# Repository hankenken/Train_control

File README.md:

# Train_control

まずは **PC＋USBカメラ1台で車両認識と画面上の模擬制御**を確認します。
[PCでの試験手順](camera_control/PC_CAMERA_TEST_JA.md)・[検証用ZIP](camera_control/dist/Train_camera_PC_test.zip)。
画面を4回クリックして検出範囲・A/Bを登録できます。制御出力は模擬ポイントとLEDで表示し、実機へは出力しません。

現在の開発は **LattePanda 3 Delta 864・Windows 10・USBカメラ2台による検証ソフト**です。
[Windows用の導入・操作手順](camera_control/README_LATTEPANDA.md)を参照してください。撮影・画像処理・画面表示・進路選択を本体上で行う試作で、実機出力はありません。

[周辺機器の低予算案](camera_control/docs/lattepanda-budget.md)と、[通信内蔵DRV8235によるポイント制御案](camera_control/output_bridge/README.md)を追加しています。
駆動回路の設計作業は保留し、先に実カメラでの認識・模擬制御を検証します。
旧Pi版・ToF・基板設計と下記の旧シミュレーターは保留・保存しています。

---

旧シミュレーターの説明：

Nゲージ路面電車向けの進路選択シミュレーター。実機・GPIO出力はありません。

## 起動

### Windowsで開く

1. Python 3を https://www.python.org/downloads/windows/ からインストールします（Python Launcherもインストール）。
2. GitHubの「Code」→「Download ZIP」でダウンロードし、ZIPを右クリックして「すべて展開」します。
3. 展開先の `start-windows.bat` をダブルクリックします。
4. 黒い画面を開いたまま、EdgeやChromeで `http://localhost:8000` を開きます。
5. 終了するときは黒い画面で Ctrl+C を押します。

`index.html` のダブルクリックではJavaScriptのモジュールが読み込まれないため、必ずサーバー経由で開いてください。

### 開発環境

Python 3とNode.js（テスト用）を使用します。外部パッケージの導入は不要です。

```sh
cd /workspace/Train_control
npm test
npm start
```

ブラウザでサーバーの8000番ポートにアクセスします。クラウド環境では公開方法が別途必要です。

## 操作

- 上側1の外側・内側：時間差方式。A→Bが設定境界未満なら直進、以上なら分岐。
- 下側2の外側・内側：LED方式。A検知から直・曲を交互表示し、B検知時の表示で決定。
- 各組の「センサA 通過」「センサB 通過」を順に押します。
- 決定後はポイントを模擬的に切り替え、進路をロックします。「通過完了」で待機へ戻します。
- 両方式とも、A検知やLEDの交互表示ではポイントを操作しません。Bで進路を確定した時点だけ位置を更新します。通過完了後も前回位置を保持します。起動直後の位置は「未確認」です。
- 設定変更は4組とも待機中の場合のみ可能です。再読み込みで状態と設定を初期化します。

図のセンサ・ポイント位置は仮配置です。交差部での線路接続はありません。
列車の速度・停止・発車は運転者が操作します。信号は進路決定の模擬表示のみで、在線・競合進路の連動は未実装です。

## 実機化の前に

ポイント駆動と車両非加工の光センサについて、[実機回路の設計案](hardware/README.md)を参照してください。未確認の電気仕様があり、まだ通電用の確定回路ではありません。

Raspberry Pi 4 Model B、KATO 40-231を基準に設計しています。
[センサとPiの配線・取付設計](hardware/sensor-design.md)、[機種・8入力の設定例](config/pi4.example.json)を追加しました。
センサの検知フィルタは単体テスト済みですが、SPI読み取り・校正画面・既存操作盤への接続はまだありません。
センサ型番と実測による校正、ポイント駆動条件、信号の仕様は今後確定します。
ポイント切替完了の確認、列車通過・在線検知、競合進路の排他、入力のチャタリング対策を追加してから実機出力を実装します。
GPIOにポイントの駆動負荷を直接接続しないでください。

ポイントの12V試作回路と部品表・試験手順は[駆動回路設計](hardware/turnout-driver.md)を参照してください。設定例の出力は無効のままで、実機GPIO制御は未実装です。

JLCPCB向けの[試作基板データ・実装依頼準備](hardware/pcb/README.md)を追加しました。
100×100mm・2層の3.3V制御基板で、8センサ入力と4系統のパルス制御を搭載します。
DRV8871と12V負荷回路は別置きです。信号灯の駆動回路は今回の基板に含みません。
DRC/ERCと回路図・基板の接続一致を確認済みですが、実機動作は未検証です。

最新のRev Cでは、4系統それぞれにパルス幅調整用の多回転トリマVRを追加しました。
目安は約50〜80msで、100ms以下になることを実機接続前に測定する必要があります。発注ZIP・PDFは`TC_IO_REVC`版を使用してください。

部品実装込みへ方針を変更しています。[PCBA用BOM/CPL草案と未確定事項](hardware/pcb/pcba/README.md)を確認してください。
現行はVRを含め表面実装50点の候補回路です。コネクタ部品を使わず、電線直結用の穴を残します。JLCPCBでの実装対応・部品番号・在庫・CPLの位置と回転が未確認のため、実装注文に使える確定セットではありません。

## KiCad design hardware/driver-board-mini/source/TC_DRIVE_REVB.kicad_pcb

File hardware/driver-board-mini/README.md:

# ポイント駆動基板 TC DRIVE Rev B 小型配置案

**60×45mm（暫定）・未配線・製造不可。100×100mmのRev Aと既存制御基板を変更せず、別リビジョンとして作成。**

基板面積は10,000→2,700mm²（73%減）。12V、DRV8871×4、表面実装35点、コネクタなし、制御3線×4組とポイント2線×4組、電源2線の9直付け位置を維持しています。
電気的なネット・部品値はRev Aと同一であることを検査しました。4回路入りの集約基板として詰めた配置案であり、実装・配線・熱設計後も維持できる最小寸法を保証するものではありません。

## 小型化の内容

- 4つのDRV8871を2×2配置。各チャンネルの入力・電流制限・デカップリング・100µFを近接配置。
- 大容量470µFと電源保護候補は上側へ集約。電解コンデンサを削除して面積だけ小さくする変更はしていません。
- 直付け穴は電源／コイル用が直径1.3mm・ランド3mm、制御用が直径1.0mm・ランド2mm。電線に引張り止めを設ける前提。
- 取付穴は**4個のM2用2.2mm穴**へ変更。外形から各3mm、中心間54×39mm。Rev AのM3とは互換ではありません。
- 三つの1mmフィデューシャルを追加。大半の部品記号をF.Fabへ移し、上面シルクはICと接続位置を優先。
- DDAのメーカー推奨ランド／マスク形状を維持し、プロジェクト専用フットプリントの熱逃がし穴を0.3mm、銅ランド0.6mmへ変更。各IC8穴でGNDに接続。

## 回路条件

53.6kΩ±1%による公称電流制限は約1.194A。メーカーVILIM範囲と抵抗誤差の計算では約1.090〜1.300A。
制御入力はGND/IN1/IN2、ポイントはOUT1=青／OUT2=白。青白は極性反転するため常設＋／−ではありません。
パルス幅とVR、B検知後だけの転換許可はTC IO側が担当。この基板だけで連続通電を防ぐ設計ではありません。
外部ヒューズ・保持型停止スイッチを通した12Vだけを使用し、1系統ずつ駆動します。
SS34、SMBJ18A、470µF/35V、100µF/35V等はまだメーカー型番・調達未確定の候補。保護協調、回生エネルギー、温度特性は未検証です。

## 検査結果

- ERC：0件。
- 回路図と基板：120端子割当が一致。
- 部品値・ネット・実装対象：Rev Aから変更なし。
- 配置段階のDRC：**0件**。銅箔間隔規則0.20mm。
- 異なるネットのパッド外接矩形による距離の最小値：0.20mm（保守的な下限計算）。配線幅や許容電流の評価ではありません。
- **未接続89件、配線0本。** 熱・電流・回生・ノイズを評価する銅配線とGND面は未実装です。

0.2mm間隔のDDA信号端子付近と、電源・負荷の太い配線、裏面GND面、熱逃がしを両立させることが次工程です。
小型化したことで放熱余裕が減る可能性があるため、配線時に面積や寸法の再調整が必要になる場合があります。
必要な露出パッドのはんだ付け、熱逃がし穴のマスク／ペースト／ビア充填の実装条件もJLCPCBと照合します。

## 資料

- `source/TC_DRIVE_REVB.kicad_sch` / `.kicad_pcb`：回路図と未配線の基板。
- `source/BOM_DRAFT.csv` / `connections.csv`：部品表・接続表。
- `review/TC_DRIVE_REVB_design_DRAFT.pdf`：概要・部品表・回路図・配置図。
- `reports/draft-checks.json`：寸法、部品数、検査範囲、ソースハッシュ。
- `build_design.py`→`verify_draft.py`→`export_documents.py`の順で再生成。

発注用ガーバー・最終BOM/CPLは出力していません。現在JLCPCBで確認中の100mm角制御基板の配置補正には影響しません。

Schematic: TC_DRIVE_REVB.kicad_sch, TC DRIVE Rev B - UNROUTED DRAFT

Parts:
C1: 470uF_35V_SMD_CANDIDATE; CP_Elec_10x10.5
C2, C4, C6, C8: 100nF_50V_X7R; C_0805_2012Metric
C3, C5, C7, C9: 100uF_35V_SMD_CANDIDATE; CP_Elec_6.3x7.7
D1: SS34_CANDIDATE; D_SMA
D2: SMBJ18A_CANDIDATE; D_SMB
J1: 12V_IN_AFTER_EXTERNAL_FUSE_AND_STOP; Power2; not fitted
J2: CONTROL_UP_OUT; Control3; not fitted
J3: CONTROL_UP_IN; Control3; not fitted
J4: CONTROL_LOW_OUT; Control3; not fitted
J5: CONTROL_LOW_IN; Control3; not fitted
J6: TURNOUT_UP_OUT; Power2; not fitted
J7: TURNOUT_UP_IN; Power2; not fitted
J8: TURNOUT_LOW_OUT; Power2; not fitted
J9: TURNOUT_LOW_IN; Power2; not fitted
R1, R2, R3, R4: 53.6k_1%; R_0805_2012Metric
R5, R7, R9, R11, R13, R15, R17, R19: 100R_1%; R_0805_2012Metric
R6, R8, R10, R12, R14, R16, R18, R20: 10k_1%; R_0805_2012Metric
U1, U2, U3, U4: DRV8871DDAR; DRV8871_DDA_ThermalVias_0p3

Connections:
GND: C1.2 (MINUS), C2.2, C3.2 (MINUS), C4.2, C5.2 (MINUS), C6.2, C7.2 (MINUS), C8.2, C9.2 (MINUS), D2.2 (A), J1.2, J2.1, J3.1, J4.1, J5.1, R1.2, R2.2, R3.2, R4.2, R6.2, R8.2, R10.2, R12.2, R14.2, R16.2, R18.2, R20.2, U1.1 (GND), U1.7 (PGND), U1.9 (EP_GND), U2.1 (GND), U2.7 (PGND), U2.9 (EP_GND), U3.1 (GND), U3.7 (PGND), U3.9 (EP_GND), U4.1 (GND), U4.7 (PGND), U4.9 (EP_GND)
LOW_IN_A: R17.2, R18.1, U4.3 (IN1)
LOW_IN_B: R19.2, R20.1, U4.2 (IN2)
LOW_IN_BLUE: J9.1, U4.6 (OUT1)
LOW_IN_ILIM: R4.1, U4.4 (ILIM)
LOW_IN_IN1: J5.2, R17.1
LOW_IN_IN2: J5.3, R19.1
LOW_IN_WHITE: J9.2, U4.8 (OUT2)
LOW_OUT_A: R13.2, R14.1, U3.3 (IN1)
LOW_OUT_B: R15.2, R16.1, U3.2 (IN2)
LOW_OUT_BLUE: J8.1, U3.6 (OUT1)
LOW_OUT_ILIM: R3.1, U3.4 (ILIM)
LOW_OUT_IN1: J4.2, R13.1
LOW_OUT_IN2: J4.3, R15.1
LOW_OUT_WHITE: J8.2, U3.8 (OUT2)
UP_IN_A: R9.2, R10.1, U2.3 (IN1)
UP_IN_B: R11.2, R12.1, U2.2 (IN2)
UP_IN_BLUE: J7.1, U2.6 (OUT1)
UP_IN_ILIM: R2.1, U2.4 (ILIM)
UP_IN_IN1: J3.2, R9.1
UP_IN_IN2: J3.3, R11.1
UP_IN_WHITE: J7.2, U2.8 (OUT2)
UP_OUT_A: R5.2, R6.1, U1.3 (IN1)
UP_OUT_B: R7.2, R8.1, U1.2 (IN2)
UP_OUT_BLUE: J6.1, U1.6 (OUT1)
UP_OUT_ILIM: R1.1, U1.4 (ILIM)
UP_OUT_IN1: J2.2, R5.1
UP_OUT_IN2: J2.3, R7.1
UP_OUT_WHITE: J6.2, U1.8 (OUT2)
VIN_12V: D1.2 (A), J1.1
VM: C1.1 (PLUS), C2.1, C3.1 (PLUS), C4.1, C5.1 (PLUS), C6.1, C7.1 (PLUS), C8.1, C9.1 (PLUS), D1.1 (K), D2.1 (K), U1.5 (VM), U2.5 (VM), U3.5 (VM), U4.5 (VM)

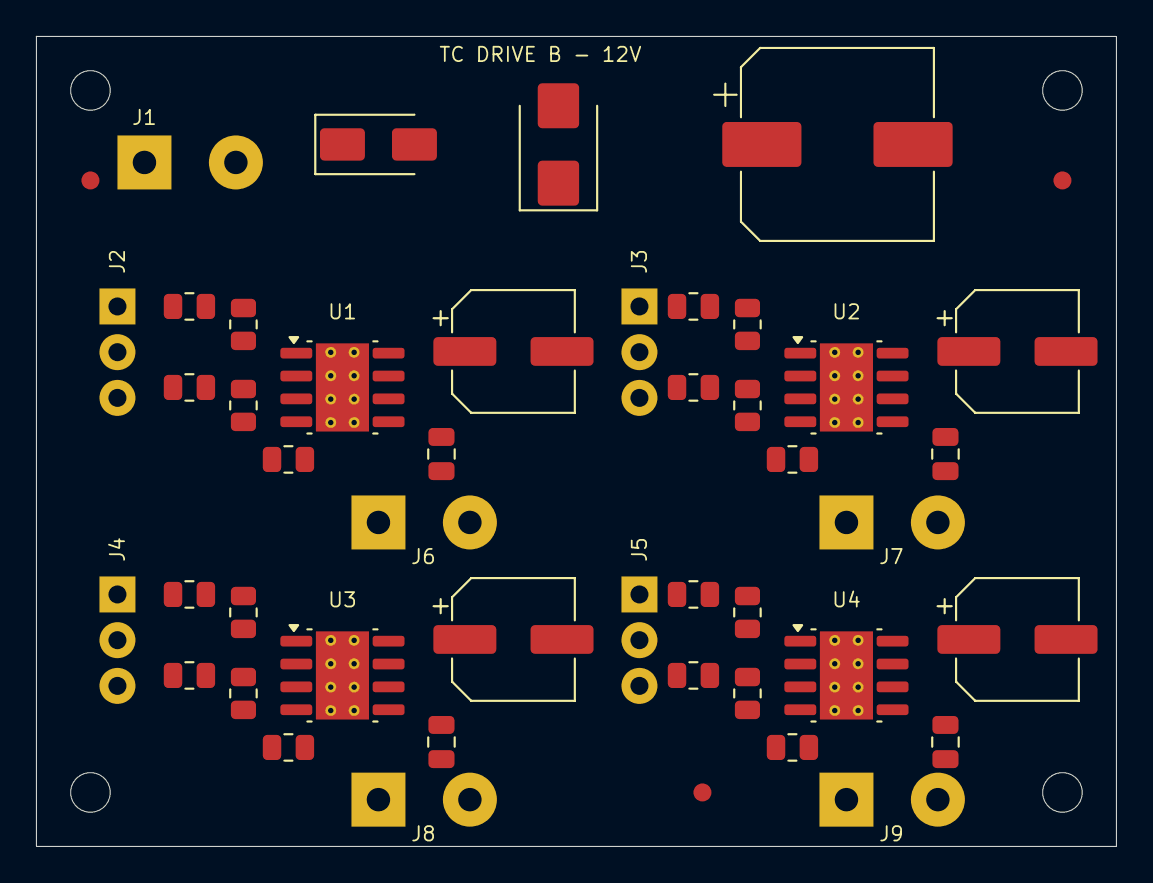
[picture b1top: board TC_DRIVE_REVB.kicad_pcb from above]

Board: 2 copper layers, 60.0 x 45.0 mm, 51 parts (0 on the bottom side), 31 nets, no tracks yet.

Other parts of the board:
FM1, FM2, FM3: Fiducial_1mm_Mask2mm
H1, H2, H3, H4: MountingHole_2.2mm_M2

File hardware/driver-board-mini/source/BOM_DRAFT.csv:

Reference,MPN_or_value,Footprint,Populate,Notes
J1,12V_IN_AFTER_EXTERNAL_FUSE_AND_STOP,TC_Wire:Power2,False,
D1,SS34_CANDIDATE,Diode_SMD:D_SMA,True,Series reverse polarity diode. Verify selected manufacturer forward loss and pulse current.
D2,SMBJ18A_CANDIDATE,Diode_SMD:D_SMB,True,Local rail clamp; pulse energy and fuse coordination not validated
C1,470uF_35V_SMD_CANDIDATE,Capacitor_SMD:CP_Elec_10x10.5,True,Bulk after polarity diode; ESR/ripple/energy verification pending
U1,DRV8871DDAR,TC_Wire:DRV8871_DDA_ThermalVias_0p3,True,TI SLVSCY9B pinout. DDA exposed pad MUST be soldered and heat-spread. Layout unrouted.
R1,53.6k_1%,Resistor_SMD:R_0805_2012Metric,True,Itrip nominal 64/53.6=1.194A; 59..69kV plus resistor 1% gives 1.090..1.300A
C2,100nF_50V_X7R,Capacitor_SMD:C_0805_2012Metric,True,Place directly at VM/PGND during final layout
C3,100uF_35V_SMD_CANDIDATE,Capacitor_SMD:CP_Elec_6.3x7.7,True,"Local bulk; candidate footprint, specific supplier part not fixed"
J2,CONTROL_UP_OUT,TC_Wire:Control3,False,Matches TC IO J10-J13 GND/IN1/IN2
J6,TURNOUT_UP_OUT,TC_Wire:Power2,False,Two-wire turnout only. Blue/white polarity not yet mapped to route.
R5,100R_1%,Resistor_SMD:R_0805_2012Metric,True,
R6,10k_1%,Resistor_SMD:R_0805_2012Metric,True,Input pulldown; driver also has internal pulldown
R7,100R_1%,Resistor_SMD:R_0805_2012Metric,True,
R8,10k_1%,Resistor_SMD:R_0805_2012Metric,True,Input pulldown; driver also has internal pulldown
U2,DRV8871DDAR,TC_Wire:DRV8871_DDA_ThermalVias_0p3,True,TI SLVSCY9B pinout. DDA exposed pad MUST be soldered and heat-spread. Layout unrouted.
R2,53.6k_1%,Resistor_SMD:R_0805_2012Metric,True,Itrip nominal 64/53.6=1.194A; 59..69kV plus resistor 1% gives 1.090..1.300A
C4,100nF_50V_X7R,Capacitor_SMD:C_0805_2012Metric,True,Place directly at VM/PGND during final layout
C5,100uF_35V_SMD_CANDIDATE,Capacitor_SMD:CP_Elec_6.3x7.7,True,"Local bulk; candidate footprint, specific supplier part not fixed"
J3,CONTROL_UP_IN,TC_Wire:Control3,False,Matches TC IO J10-J13 GND/IN1/IN2
J7,TURNOUT_UP_IN,TC_Wire:Power2,False,Two-wire turnout only. Blue/white polarity not yet mapped to route.
R9,100R_1%,Resistor_SMD:R_0805_2012Metric,True,
R10,10k_1%,Resistor_SMD:R_0805_2012Metric,True,Input pulldown; driver also has internal pulldown
R11,100R_1%,Resistor_SMD:R_0805_2012Metric,True,
R12,10k_1%,Resistor_SMD:R_0805_2012Metric,True,Input pulldown; driver also has internal pulldown
U3,DRV8871DDAR,TC_Wire:DRV8871_DDA_ThermalVias_0p3,True,TI SLVSCY9B pinout. DDA exposed pad MUST be soldered and heat-spread. Layout unrouted.
R3,53.6k_1%,Resistor_SMD:R_0805_2012Metric,True,Itrip nominal 64/53.6=1.194A; 59..69kV plus resistor 1% gives 1.090..1.300A
C6,100nF_50V_X7R,Capacitor_SMD:C_0805_2012Metric,True,Place directly at VM/PGND during final layout
C7,100uF_35V_SMD_CANDIDATE,Capacitor_SMD:CP_Elec_6.3x7.7,True,"Local bulk; candidate footprint, specific supplier part not fixed"
J4,CONTROL_LOW_OUT,TC_Wire:Control3,False,Matches TC IO J10-J13 GND/IN1/IN2
J8,TURNOUT_LOW_OUT,TC_Wire:Power2,False,Two-wire turnout only. Blue/white polarity not yet mapped to route.
R13,100R_1%,Resistor_SMD:R_0805_2012Metric,True,
R14,10k_1%,Resistor_SMD:R_0805_2012Metric,True,Input pulldown; driver also has internal pulldown
R15,100R_1%,Resistor_SMD:R_0805_2012Metric,True,
R16,10k_1%,Resistor_SMD:R_0805_2012Metric,True,Input pulldown; driver also has internal pulldown
U4,DRV8871DDAR,TC_Wire:DRV8871_DDA_ThermalVias_0p3,True,TI SLVSCY9B pinout. DDA exposed pad MUST be soldered and heat-spread. Layout unrouted.
R4,53.6k_1%,Resistor_SMD:R_0805_2012Metric,True,Itrip nominal 64/53.6=1.194A; 59..69kV plus resistor 1% gives 1.090..1.300A
C8,100nF_50V_X7R,Capacitor_SMD:C_0805_2012Metric,True,Place directly at VM/PGND during final layout
C9,100uF_35V_SMD_CANDIDATE,Capacitor_SMD:CP_Elec_6.3x7.7,True,"Local bulk; candidate footprint, specific supplier part not fixed"
J5,CONTROL_LOW_IN,TC_Wire:Control3,False,Matches TC IO J10-J13 GND/IN1/IN2
J9,TURNOUT_LOW_IN,TC_Wire:Power2,False,Two-wire turnout only. Blue/white polarity not yet mapped to route.
R17,100R_1%,Resistor_SMD:R_0805_2012Metric,True,
R18,10k_1%,Resistor_SMD:R_0805_2012Metric,True,Input pulldown; driver also has internal pulldown
R19,100R_1%,Resistor_SMD:R_0805_2012Metric,True,
R20,10k_1%,Resistor_SMD:R_0805_2012Metric,True,Input pulldown; driver also has internal pulldown
#FLG01,PWR_FLAG_VM,,False,"Schematic-only annotation: VM is supplied through D1, not a physical source"

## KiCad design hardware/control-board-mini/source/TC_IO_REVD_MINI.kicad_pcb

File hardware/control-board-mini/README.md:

# TC IO Rev D MINI — ToF対応の小型制御基板案

**50×40mm（配線前の暫定寸法）・未配線・発注不可。**
100×100mm Rev Cを保存し、ユーザーの小型化とToF指定に合わせた別リビジョンです。
面積は10,000→2,000mm²（80%減）。コネクタ部品なし、実装46点。
全体の物理的最小寸法を証明したものではなく、2層配線・実装条件の確認で寸法が変わる可能性があります。

## 電気回路の変更

- ポイント4系統のワンショット・個別VR・方向ゲート・電源監視を維持。
- ユーザー指定のC2167387（470nF±10%）と個別VRでの概略時間調整を維持。
- ToFはI2Cで接続するため、MCP3008（U1）、ADC用R5、C5、C12を削除。
- SPIのMOSI/MISO/SCLK/CS配線と、アナログセンサ端子・JP1を削除。
- Pi GPIO2/3のI2Cは維持。VL53L4CD×8は別のI2C切替・電源基板経由で接続する計画。
- ToF切替・電源基板はまだ設計確定していない。Piの3.3Vから8台のセンサを直接給電する構成ではない。

旧アナログ用バッファ基板はToF方式では使用しません。旧Rev Cは変更しておらず、小型版に切り替えると現在のJLCPCB配置補正は流用できません。

## 基板接続の再番号付け

**J1はPiの40端子番号と一致しません。** `source/pi-wiring.csv`を必ず使います。
旧40穴から使用信号17点＋NC1穴の2×9直付けパッドへ縮小。重複GNDは1本に集約。
3.3Vの制御・I2C回路だけのGNDで、コイル電流を通しません。

| 本基板の位置 | 配線 |
|---|---|
| J1 | Pi直付け配線。1〜17番はpi-wiring.csv参照、18番NC |
| J3 | 1=GND、2/3=UP_OUT IN1/IN2、4/5=UP_IN IN1/IN2、6/7=LOW_OUT IN1/IN2、8/9=LOW_IN IN1/IN2、10番NC |
| J4 | 1=GND、2=Pi側3.3Vロジック、3=SDA、4=SCL。ToF切替基板のホスト側へ |
| TP1 | 1=GND、2=CLEAR_N、3=POWER_GOOD、4=UP_OUT_Q、5=UP_IN_Q、6=LOW_OUT_Q、7=LOW_IN_Q |

J4の2番はホスト側ロジック用。専用センサ電源の3.3V出力をPiの3.3Vへ並列接続しません。
I2C切替基板の電源順序・逆給電・ケーブル容量・通信速度は次工程です。

### 小型駆動基板との配線

| 制御IO MINI | DRIVE MINI |
|---|---|
| J3-1 GND | J2/J3/J4/J5の各1番へ分配 |
| J3-2 / J3-3 | 駆動J2の2番/3番 |
| J3-4 / J3-5 | 駆動J3の2番/3番 |
| J3-6 / J3-7 | 駆動J4の2番/3番 |
| J3-8 / J3-9 | 駆動J5の2番/3番 |

**基板ごとのJ1/J3は別物です。駆動基板J1は12V入力なので、制御基板J1へ接続しません。**

## 実装と機械条件

- 2層の配置案、M2用2.2mm穴4個。中心（2.5,2.5）、（47.5,2.5）、（2.5,37.5）、（47.5,37.5）mm。
- 旧100mm角・M3固定穴とは互換なし。
- 信号直付けパッドは2mmピッチ、穴0.8mm、ランド1.4mm。26〜28AWG程度を初期想定し、実際の電線外径・はんだ付け・引張り止めを確認。
- TP1は1.2mmの表面測定パッド。細いプローブで測定し、コネクタは付けない。
- 抵抗・コンデンサ等の記号はF.Fab中心。組立図と配線表で位置を照合。
- 部品モデル、吸着原点とJLCPCB回転は新しい基板で再確認。

## 確認済み／未完了

回路図・配置のERC/DRC、保持する46実装部品とRev Cの電気接続の一致を検査します。
配線・GND面・実機試験・JLCPCBモデルの照合は未完了。製造ガーバーは出力しません。
ToFドライバ、I2C切替、距離status判定の実機ソフトはまだ実装されていません。従来のシミュレータを実機ToF制御済みと扱いません。

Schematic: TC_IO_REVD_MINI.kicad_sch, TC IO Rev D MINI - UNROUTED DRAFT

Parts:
C1, C2, C3, C4: 470nF_10%_X7R_50V; C_1206_3216Metric
C6, C7, C8, C9, C10, C11: 100nF_X7R_50V; C_0805_2012Metric
C13: 10uF_X7R_25V; C_1206_3216Metric
J1: PI_DIRECT_RENUMBERED; Pads2x09; not fitted
J3: DRIVER_BUS; Pads2x05; not fitted
J4: I2C_BUS; Pads2x02; not fitted
R1, R2, R3, R4: 150k_1%; R_0805_2012Metric
R6, R7, R8, R9, R10, R11, R12, R13, R14, R15, R16, R17, R18, R19, R20, R21, R22, R23, R24, R25, R26: 10k_1%; R_0805_2012Metric
TP1: TEST_BUS; Probe1x07; not fitted
U2, U3: CD74HC221M96; SOIC-16_3.9x9.9mm_P1.27mm
U4, U5, U6: SN74HC08DR; SOIC-14_3.9x8.7mm_P1.27mm
U7: MCP100T-300I/TT; SOT-23
VR1, VR2, VR3, VR4: 3224W-1-104E; Potentiometer_Bourns_3224W_Vertical

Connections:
+3V3: C6.1, C7.1, C8.1, C9.1, C10.1, C11.1, C13.1, J1.1 (PI_PHYS_1), J4.2, R1.1, R2.1, R3.1, R4.1, U2.16 (VCC), U3.16 (VCC), U4.14 (VCC), U5.14 (VCC), U6.14, U7.2 (VDD)
ARM: J1.8 (PI_PHYS_16), R18.1, U6.1
CLEAR_N: TP1.2, U2.3 (CLR_N), U2.11 (CLR_N), U3.3 (CLR_N), U3.11 (CLR_N), U6.3
GND: C6.2, C7.2, C8.2, C9.2, C10.2, C11.2, C13.2, J1.4 (PI_PHYS_6), J3.1, J4.1, R6.2, R7.2, R8.2, R9.2, R10.2, R11.2, R12.2, R13.2, R14.2, R15.2, R16.2, R17.2, R18.2, R19.2, R20.2, R21.2, R22.2, R23.2, R24.2, R25.2, R26.2, TP1.1, U2.1 (A_N), U2.8 (GND), U2.9 (A_N), U3.1 (A_N), U3.8 (GND), U3.9 (A_N), U4.7 (GND), U5.7 (GND), U6.4, U6.5, U6.7, U6.9, U6.10, U6.12, U6.13, U7.3 (VSS)
LOW_IN_ADJ: R4.2, VR4.1 (CCW)
LOW_IN_CE: C4.1, U3.6 (CEXT)
LOW_IN_IN1: J3.8, R25.1, U5.8 (3Y)
LOW_IN_IN2: J3.9, R26.1, U5.11 (4Y)
LOW_IN_N: J1.6 (PI_PHYS_13), R16.1, U5.12 (4A)
LOW_IN_P: J1.5 (PI_PHYS_11), R15.1, U5.9 (3A)
LOW_IN_Q: TP1.7, U3.5 (Q), U5.10 (3B), U5.13 (4B)
LOW_IN_RC: C4.2, U3.7 (RCEXT), VR4.2 (WIPER), VR4.3 (CW)
LOW_IN_TRIG: J1.7 (PI_PHYS_15), R17.1, U3.10 (B)
LOW_OUT_ADJ: R3.2, VR3.1 (CCW)
LOW_OUT_CE: C3.1, U3.14 (CEXT)
LOW_OUT_IN1: J3.6, R23.1, U5.3 (1Y)
LOW_OUT_IN2: J3.7, R24.1, U5.6 (2Y)
LOW_OUT_N: J1.17 (PI_PHYS_40), R13.1, U5.4 (2A)
LOW_OUT_P: J1.16 (PI_PHYS_38), R12.1, U5.1 (1A)
LOW_OUT_Q: TP1.6, U3.13 (Q), U5.2 (1B), U5.5 (2B)
LOW_OUT_RC: C3.2, U3.15 (RCEXT), VR3.2 (WIPER), VR3.3 (CW)
LOW_OUT_TRIG: J1.15 (PI_PHYS_37), R14.1, U3.2 (B)
POWER_GOOD: TP1.3, U6.2, U7.1 (RESET_N)
SCL: J1.3 (PI_PHYS_5), J4.4
SDA: J1.2 (PI_PHYS_3), J4.3
UP_IN_ADJ: R2.2, VR2.1 (CCW)
UP_IN_CE: C2.1, U2.6 (CEXT)
UP_IN_IN1: J3.4, R21.1, U4.8 (3Y)
UP_IN_IN2: J3.5, R22.1, U4.11 (4Y)
UP_IN_N: J1.14 (PI_PHYS_36), R10.1, U4.12 (4A)
UP_IN_P: J1.12 (PI_PHYS_33), R9.1, U4.9 (3A)
UP_IN_Q: TP1.5, U2.5 (Q), U4.10 (3B), U4.13 (4B)
UP_IN_RC: C2.2, U2.7 (RCEXT), VR2.2 (WIPER), VR2.3 (CW)
UP_IN_TRIG: J1.13 (PI_PHYS_35), R11.1, U2.10 (B)
UP_OUT_ADJ: R1.2, VR1.1 (CCW)
UP_OUT_CE: C1.1, U2.14 (CEXT)
UP_OUT_IN1: J3.2, R19.1, U4.3 (1Y)
UP_OUT_IN2: J3.3, R20.1, U4.6 (2Y)
UP_OUT_N: J1.10 (PI_PHYS_31), R7.1, U4.4 (2A)
UP_OUT_P: J1.9 (PI_PHYS_29), R6.1, U4.1 (1A)
UP_OUT_Q: TP1.4, U2.13 (Q), U4.2 (1B), U4.5 (2B)
UP_OUT_RC: C1.2, U2.15 (RCEXT), VR1.2 (WIPER), VR1.3 (CW)
UP_OUT_TRIG: J1.11 (PI_PHYS_32), R8.1, U2.2 (B)

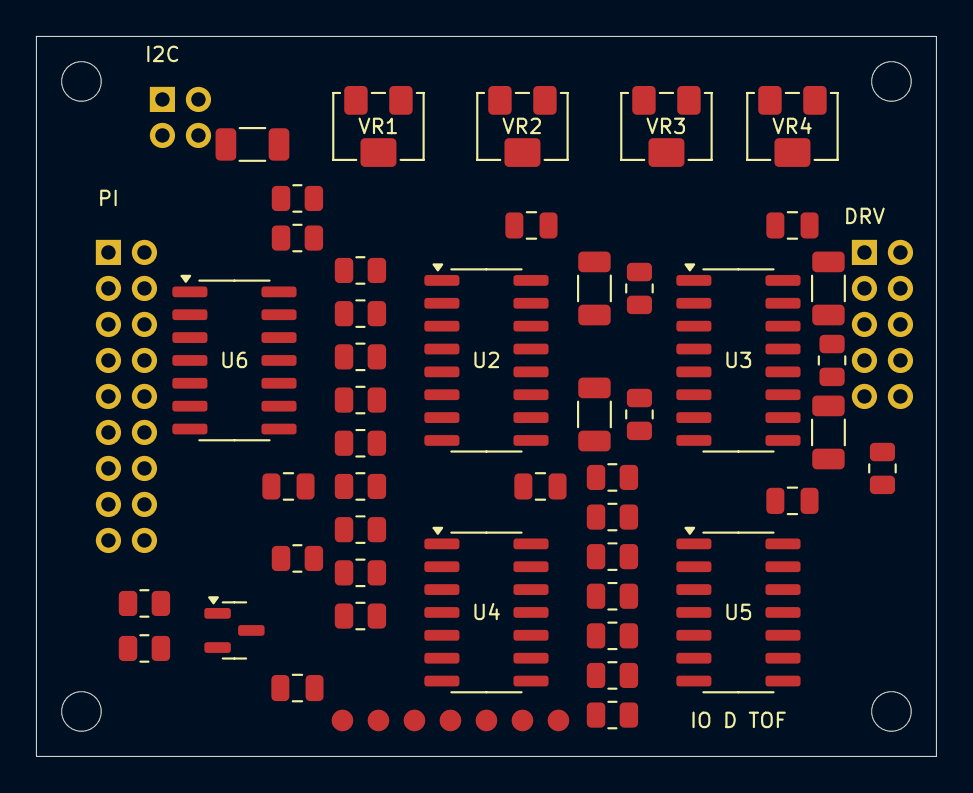
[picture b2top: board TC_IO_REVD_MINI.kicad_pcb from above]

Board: 2 copper layers, 50.0 x 40.0 mm, 54 parts (0 on the bottom side), 43 nets, no tracks yet.

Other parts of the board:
H1, H2, H3, H4: MountingHole_2.2mm_M2

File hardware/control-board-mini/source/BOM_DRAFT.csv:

Reference,MPN_or_value,Footprint,Populate,Notes
U2,CD74HC221M96,Package_SO:SOIC-16_3.9x9.9mm_P1.27mm,True,"HC, NOT LS/HCT. Timing RC unverified at 3.3V: measure before load connection"
U3,CD74HC221M96,Package_SO:SOIC-16_3.9x9.9mm_P1.27mm,True,"HC, NOT LS/HCT. Timing RC unverified at 3.3V: measure before load connection"
U4,SN74HC08DR,Package_SO:SOIC-14_3.9x8.7mm_P1.27mm,True,
U5,SN74HC08DR,Package_SO:SOIC-14_3.9x8.7mm_P1.27mm,True,
U6,SN74HC08DR,Package_SO:SOIC-14_3.9x8.7mm_P1.27mm,True,
U7,MCP100T-300I/TT,Package_TO_SOT_SMD:SOT-23,True,"RESET_N=pin1,VDD=pin2,VSS=pin3 checked against user-supplied Microchip DS11187F; bench power-ramp testing pending"
R6,10k_1%,Resistor_SMD:R_0805_2012Metric,True,Individual SMT pulldown replacing the former SIP resistor networks
R7,10k_1%,Resistor_SMD:R_0805_2012Metric,True,Individual SMT pulldown replacing the former SIP resistor networks
R8,10k_1%,Resistor_SMD:R_0805_2012Metric,True,Individual SMT pulldown replacing the former SIP resistor networks
R9,10k_1%,Resistor_SMD:R_0805_2012Metric,True,Individual SMT pulldown replacing the former SIP resistor networks
R10,10k_1%,Resistor_SMD:R_0805_2012Metric,True,Individual SMT pulldown replacing the former SIP resistor networks
R11,10k_1%,Resistor_SMD:R_0805_2012Metric,True,Individual SMT pulldown replacing the former SIP resistor networks
R12,10k_1%,Resistor_SMD:R_0805_2012Metric,True,Individual SMT pulldown replacing the former SIP resistor networks
R13,10k_1%,Resistor_SMD:R_0805_2012Metric,True,Individual SMT pulldown replacing the former SIP resistor networks
R14,10k_1%,Resistor_SMD:R_0805_2012Metric,True,Individual SMT pulldown replacing the former SIP resistor networks
R15,10k_1%,Resistor_SMD:R_0805_2012Metric,True,Individual SMT pulldown replacing the former SIP resistor networks
R16,10k_1%,Resistor_SMD:R_0805_2012Metric,True,Individual SMT pulldown replacing the former SIP resistor networks
R17,10k_1%,Resistor_SMD:R_0805_2012Metric,True,Individual SMT pulldown replacing the former SIP resistor networks
R18,10k_1%,Resistor_SMD:R_0805_2012Metric,True,Individual SMT pulldown replacing the former SIP resistor networks
R19,10k_1%,Resistor_SMD:R_0805_2012Metric,True,Individual SMT pulldown replacing the former SIP resistor networks
R20,10k_1%,Resistor_SMD:R_0805_2012Metric,True,Individual SMT pulldown replacing the former SIP resistor networks
R21,10k_1%,Resistor_SMD:R_0805_2012Metric,True,Individual SMT pulldown replacing the former SIP resistor networks
R22,10k_1%,Resistor_SMD:R_0805_2012Metric,True,Individual SMT pulldown replacing the former SIP resistor networks
R23,10k_1%,Resistor_SMD:R_0805_2012Metric,True,Individual SMT pulldown replacing the former SIP resistor networks
R24,10k_1%,Resistor_SMD:R_0805_2012Metric,True,Individual SMT pulldown replacing the former SIP resistor networks
R25,10k_1%,Resistor_SMD:R_0805_2012Metric,True,Individual SMT pulldown replacing the former SIP resistor networks
R26,10k_1%,Resistor_SMD:R_0805_2012Metric,True,Individual SMT pulldown replacing the former SIP resistor networks
R1,150k_1%,Resistor_SMD:R_0805_2012Metric,True,
VR1,3224W-1-104E,Potentiometer_SMD:Potentiometer_Bourns_3224W_Vertical,True,"100k multi-turn trimmer, series with 150k. Wiper pin2 tied to pin3; verify CW direction and pulse width on bench"
C1,470nF_10%_X7R_50V,Capacitor_SMD:C_1206_3216Metric,True,"Floating timing MLCC: CEXT to RCEXT. Verify DC bias, temperature and actual pulse width; no guaranteed timing limit"
R2,150k_1%,Resistor_SMD:R_0805_2012Metric,True,
VR2,3224W-1-104E,Potentiometer_SMD:Potentiometer_Bourns_3224W_Vertical,True,"100k multi-turn trimmer, series with 150k. Wiper pin2 tied to pin3; verify CW direction and pulse width on bench"
C2,470nF_10%_X7R_50V,Capacitor_SMD:C_1206_3216Metric,True,"Floating timing MLCC: CEXT to RCEXT. Verify DC bias, temperature and actual pulse width; no guaranteed timing limit"
R3,150k_1%,Resistor_SMD:R_0805_2012Metric,True,
VR3,3224W-1-104E,Potentiometer_SMD:Potentiometer_Bourns_3224W_Vertical,True,"100k multi-turn trimmer, series with 150k. Wiper pin2 tied to pin3; verify CW direction and pulse width on bench"
C3,470nF_10%_X7R_50V,Capacitor_SMD:C_1206_3216Metric,True,"Floating timing MLCC: CEXT to RCEXT. Verify DC bias, temperature and actual pulse width; no guaranteed timing limit"
R4,150k_1%,Resistor_SMD:R_0805_2012Metric,True,
VR4,3224W-1-104E,Potentiometer_SMD:Potentiometer_Bourns_3224W_Vertical,True,"100k multi-turn trimmer, series with 150k. Wiper pin2 tied to pin3; verify CW direction and pulse width on bench"
C4,470nF_10%_X7R_50V,Capacitor_SMD:C_1206_3216Metric,True,"Floating timing MLCC: CEXT to RCEXT. Verify DC bias, temperature and actual pulse width; no guaranteed timing limit"
C6,100nF_X7R_50V,Capacitor_SMD:C_0805_2012Metric,True,IC bypass; keep close
C7,100nF_X7R_50V,Capacitor_SMD:C_0805_2012Metric,True,IC bypass; keep close
C8,100nF_X7R_50V,Capacitor_SMD:C_0805_2012Metric,True,IC bypass; keep close
C9,100nF_X7R_50V,Capacitor_SMD:C_0805_2012Metric,True,IC bypass; keep close
C10,100nF_X7R_50V,Capacitor_SMD:C_0805_2012Metric,True,IC bypass; keep close
C11,100nF_X7R_50V,Capacitor_SMD:C_0805_2012Metric,True,IC bypass; keep close
C13,10uF_X7R_25V,Capacitor_SMD:C_1206_3216Metric,True,Nonpolar MLCC bulk bypass; check effective capacitance
J1,PI_DIRECT_RENUMBERED,TC_Wire:Pads2x09,False,"NEW NUMBERING: 17 used Pi signals plus NC18, see pi-wiring.csv. NOT a 40-pin Pi connector."
J3,DRIVER_BUS,TC_Wire:Pads2x05,False,"1 GND,2..9 channel IN1/IN2 pairs;10 NC. No 12V here."
J4,I2C_BUS,TC_Wire:Pads2x02,False,
TP1,TEST_BUS,TC_Wire:Probe1x07,False,
